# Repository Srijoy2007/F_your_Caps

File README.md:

Bobby-Pad is a 9 switches budget macro-keyboard with a great quality...

#PROJECT DETAILS ->
    1. PCB :- the pcb is based of RP2040 , the pcb has the basic structure of any RP2040 PCB 
              it contains a USB C recptable support , Along with it it contains a Rotary Encoder 
	      switch and a 2.3cm OLED. 
    2. FIRMWARE :- Since RP2040 doesen't support QMK so I am builduing a custom FIRMWARE with Rust(will update it soon)
    3. CASE & PLATE :- For the Case and plate I am planning for alimunium to give it a weight , the design still under process

# ROAD MAP ->
  
  -> First commit the V1 with STM32 [ 05/22] { STM32 doesnt fit into the budget}
  -> Second change V2 with RP2040 [06/22] {Had issue with position and connections}
  -> Third change V3 with RP2040 [06/22]  { 0 errors }

#My thoughts ->
 * I built the Version 1 without knowing much about its price but when I knew that I was shocked so I switched to RP2040 which was not 
   that difficult to adapt as it has a good datasheet and guide provided in its official website , but this mcu is not much supported by 
   the keyboard community still I feel comfortable to use this one . I ordered a Raberry Pi PICO for dry run and testing the firmware code 
   before putting it to the PCBs (Might upload pics of it). 

#BUDGET -> 
 
 * PCB build + Bottom Assembly : 44$ FOR 5 PCB (i.e. Rs. 3,432) 
 * SWITCHES (Cherry MX RGB blue) : 26$ FOR 50 switches (i.e. Rs.2,025)
 * Rotary encoder + oled :  8$ - 9$  per keeb :- total 40$ - 45$ for 5 keeb
 * Case & plate : --

  #CURRENT TOTAL FOR EACH KEYBOARD (NO PLATE &  CASE) : 24$ build cost 
#TO-DO ->
 [X] PCB design
 [x] PCB Test
 [ ] Firmware test/build 
 [ ] Case and plate design 
 [ ] Final test

* All the pcb related files are uploaded

© 2022 GitHub, Inc.
Terms
Privacy
Security
Status
Docs
Contact GitHub
Pricing
API
Training
Blog
About

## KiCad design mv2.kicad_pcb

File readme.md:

Bobby-Pad is a 9 switches budget macro-keyboard with a great quality...

#PROJECT DETAILS ->
    1. PCB :- the pcb is based of RP2040 , the pcb has the basic structure of any RP2040 PCB 
              it contains a USB C recptable support , Along with it it contains a Rotary Encoder 
	      switch and a 2.3cm OLED. 
    
    2. FIRMWARE :- Since RP2040 doesen't support QMK so I am builduing a custom FIRMWARE with Rust(will update it soon)

    3. CASE & PLATE :- For the Case and plate I am planning for alimunium to give it a weight , the design still under process

# ROAD MAP ->
  
  -> First commit the V1 with STM32 [ 05/22] { STM32 doesnt fit into the budget}
  -> Second change V2 with RP2040 [06/22] {Had issue with position and connections}
  -> Third change V3 with RP2040 [06/22]  { 0 errors }

#My thoughts ->
 * I built the Version 1 without knowing much about its price but when I knew that I was shocked so I switched to RP2040 which was not 
   that difficult to adapt as it has a good datasheet and guide provided in its official website , but this mcu is not much supported by 
   the keyboard community still I feel comfortable to use this one . I ordered a Raberry Pi PICO for dry run and testing the firmware code 
   before putting it to the PCBs (Might upload pics of it). 

#BUDGET -> 
 
 * PCB build + Bottom Assembly : 44$ FOR 5 PCB (i.e. Rs. 3,432) 
 * SWITCHES (Cherry MX RGB blue) : 26$ FOR 50 switches (i.e. Rs.2,025)
 * Rotary encoder + oled :  8$ - 9$  per keeb :- total 40$ - 45$ for 5 keeb
 * Case & plate : --

  #CURRENT TOTAL FOR EACH KEYBOARD (NO PLATE &  CASE) : 24$ build cost 
#TO-DO ->
 [X] PCB design
 [x] PCB Test
 [ ] Firmware test/build 
 [ ] Case and plate design 
 [ ] Final test

* All the pcb related files are uploaded

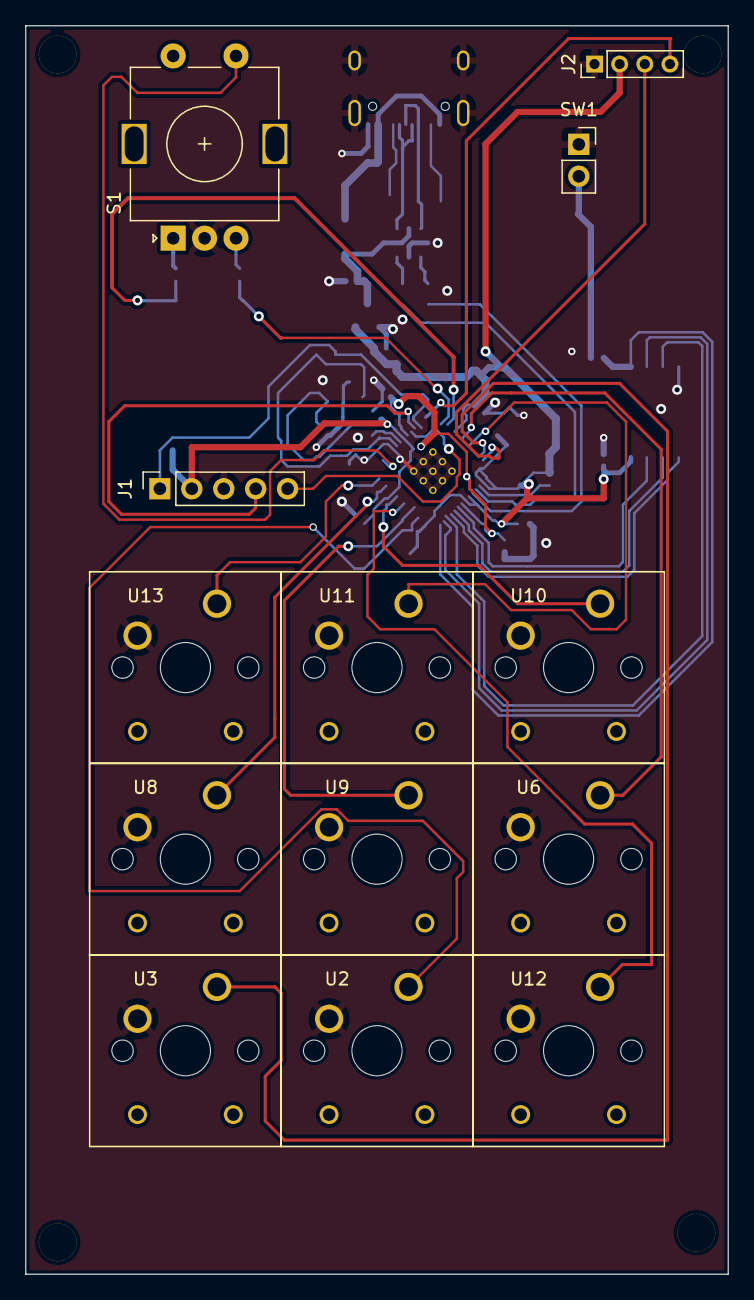
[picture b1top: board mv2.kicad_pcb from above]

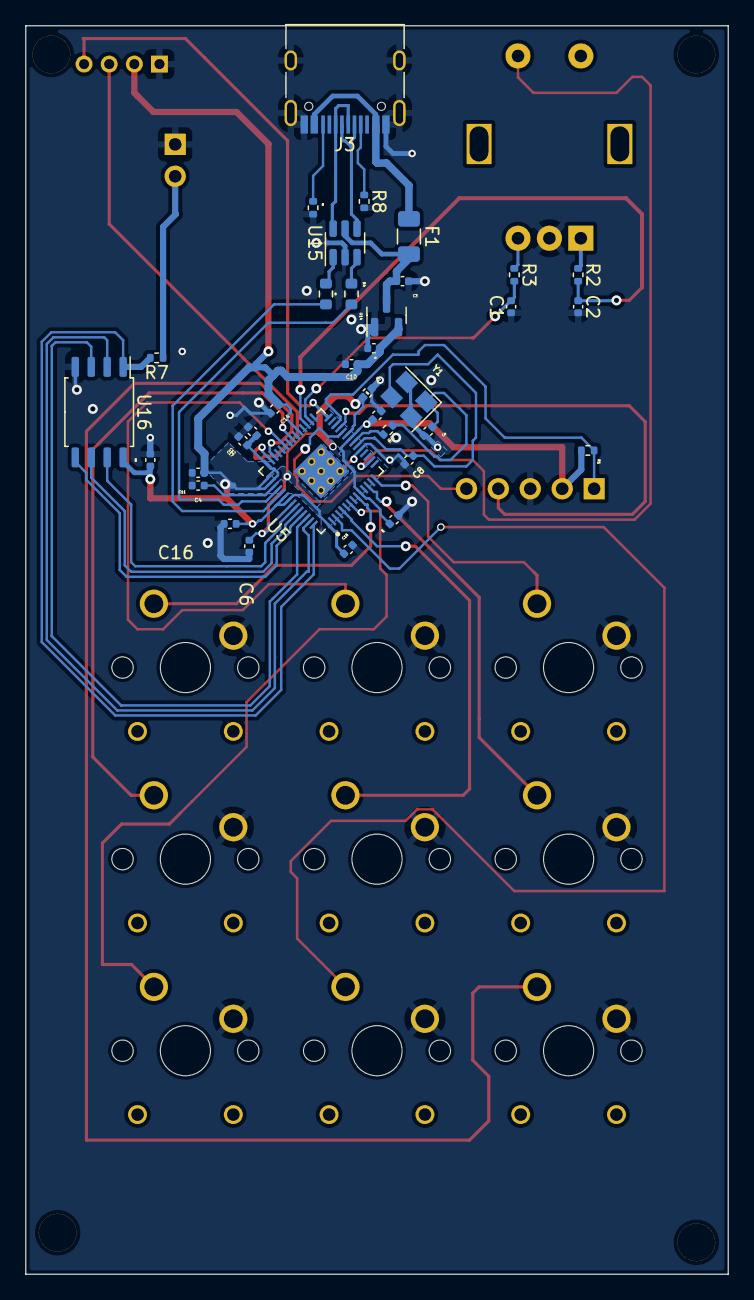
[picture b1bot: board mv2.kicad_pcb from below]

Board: 2 copper layers, 55.9 x 99.3 mm, 48 parts (35 on the bottom side), 42 nets.

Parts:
C1, C2, C6, C7, C12, C13, C14, C15, C16, C17, C18, C19: 100nF; C_0402_1005Metric
C3, C4, C5, C11: 1uF; C_0402_1005Metric
C8: 22pF; C_0402_1005Metric
C10: 10uF; C_0402_1005Metric
Ce: 22pF; C_0402_1005Metric
F1: 500mA; Fuse_1206_3216Metric
J1: SWD; PinSocket_1x05_P2.54mm_Vertical
J2: Conn_01x04; PinHeader_1x04_P2.00mm_Vertical
J3: USB_C_Receptacle_USB2.0; USB_C_Receptacle_HRO_TYPE-C-31-M-12
R1, R6, R7: 1k; R_0402_1005Metric
R2, R3: 27k; R_0402_1005Metric
R4, R5: 27R; R_0603_1608Metric
R8, R9: 5k1; R_0402_1005Metric
S1: ENCODER-SWITCH; RotaryEncoder_Alps_EC11E-Switch_Vertical_H20mm
SW1: SW_Push; PinSocket_1x02_P2.54mm_Vertical
U2, U3, U6, U8, U9, U10, U11, U12, U13: MX1A-11NN; CHERRY_MX1A-11NN_SWITCH
U5: RP2040; QFN40P700X700X90-57N
U14: XC6206PxxxMR-Regulator_Linear; SOT-23
U15: USBLC6-2SC6; SOT-23-6
U16: W25Q128JVS; SOIC-8_5.23x5.23mm_P1.27mm
Y1: 12MHz; Crystal_SMD_3225-4Pin_3.2x2.5mm

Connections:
+1V1: C4.1, C6.1, C7.1, U5.23 (DVDD), U5.45 (VREG_VOUT), U5.50 (DVDD)
+3V3: C5.2, C10.1, C11.1, C12.1, C13.1, C14.1, C15.1, C16.1, C17.1, C18.1, C19.1, J1.2, J2.2, R1.1, U5.1 (IOVDD), U5.10 (IOVDD), U5.22 (IOVDD), U5.33 (IOVDD), U5.42 (IOVDD), U5.43 (ADC_AVDD), U5.44 (VREG_VIN), U5.48 (USB_VDD), U5.49 (IOVDD), U14.2 (VO), U16.8 (VCC)
+5V: C3.2, F1.2, U14.3 (VI), U15.5 (VBUS)
/But_1: U2.P$1, U5.3 (GPIO1)
/But_2: U5.5 (GPIO3), U9.P$1
/But_3: U5.7 (GPIO5), U12.P$1
/But_4: U3.P$1, U5.40 (GPIO28/ADC2)
/But_6: U5.9 (GPIO7), U10.P$1
/But_8: U5.12 (GPIO9), U8.P$1
/But_9: U5.14 (GPIO11), U13.P$1
/But_11: U5.35 (GPIO23), U6.P$1
/But_12: U5.37 (GPIO25), U11.P$1
/CC2: J3.B5 (CC2), R9.1
/GPIO19: C1.2, R3.2, U5.30 (GPIO19)
/GPIO20: C2.1, R2.2, U5.31 (GPIO20)
/XTAL_O: Ce.2, R6.1, Y1.1
/~USB_BOOT: R7.1, SW1.2
CS: R7.2, U5.56 (QSPI_CSN), U16.1 (~CS)
D_N: R4.1, U15.3 (I/O2)
D_P: R5.1, U15.1 (I/O1)
D_USB_N: J3.A7 (D-), J3.B7 (D-), U15.4 (I/O2)
D_USB_P: J3.A6 (D+), J3.B6 (D+), U15.6 (I/O1)
GND: C1.1, C2.2, C3.1, C4.2, C5.1, C6.2, C7.2, C8.1, C10.2, C11.2, C12.2, C13.2, C14.2, C15.2, C16.2, C17.2, C18.2, C19.2, Ce.1, J1.3, J2.1, J3.A1 (GND), J3.A12 (GND), J3.B1 (GND), J3.B12 (GND), J3.S1 (SHIELD), R8.2, R9.2, S1.C, SW1.1, U2.P$2, U3.P$2, U5.19 (TESTEN), U5.57 (GND), U6.P$2, U8.P$2, U9.P$2, U10.P$2, U11.P$2, U12.P$2, U13.P$2, U14.1 (GND), U15.2 (GND), U16.4 (GND), Y1.2, Y1.4
GPI0 17: J2.4, U5.28 (GPIO17)
GPIO21: S1.S1, U5.16 (GPIO13)
GPIO 18: J2.3, U5.41 (GPIO29/ADC3)
unnamed: J3.A5 (CC1), R8.1
unnamed: R2.1, S1.A
unnamed: R3.1, S1.B
unnamed: R4.2, U5.46 (USB_DM)
unnamed: R5.2, U5.47 (USB_DP)
QSPI_CLK: U5.52 (QSPI_SCLK), U16.6 (CLK)
SD0: U5.53 (QSPI_SD0), U16.5 (DI(IO0))
SD1: U5.55 (QSPI_SD1), U16.2 (DO(IO1))
SD2: U5.54 (QSPI_SD2), U16.3 (IO2)
SD3: U5.51 (QSPI_SD3), U16.7 (IO3)
SWCLK: J1.5, U5.24 (SWCLK)
SWD: J1.4, U5.25 (SWD)
VBUS: F1.1, J3.A4 (VBUS), J3.A9 (VBUS), J3.B4 (VBUS), J3.B9 (VBUS)
XTAL_IN: C8.2, U5.20 (XIN), Y1.3
XTAL_OUT: R6.2, U5.21 (XOUT)
~RESET: J1.1, R1.2, U5.26 (RUN)

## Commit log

2022-06-02 Add files via upload
    New , pcb and schematic with the RP2040 micro - controller
2022-06-06 pcb routed
2022-06-10 Add files via upload
    A 9 key dev tool made with rp2040 version 3
    (prototype)
2022-06-14 Version 3 final version of the pcb
2022-07-06 Add files via upload
    QMK firmware v1 files
